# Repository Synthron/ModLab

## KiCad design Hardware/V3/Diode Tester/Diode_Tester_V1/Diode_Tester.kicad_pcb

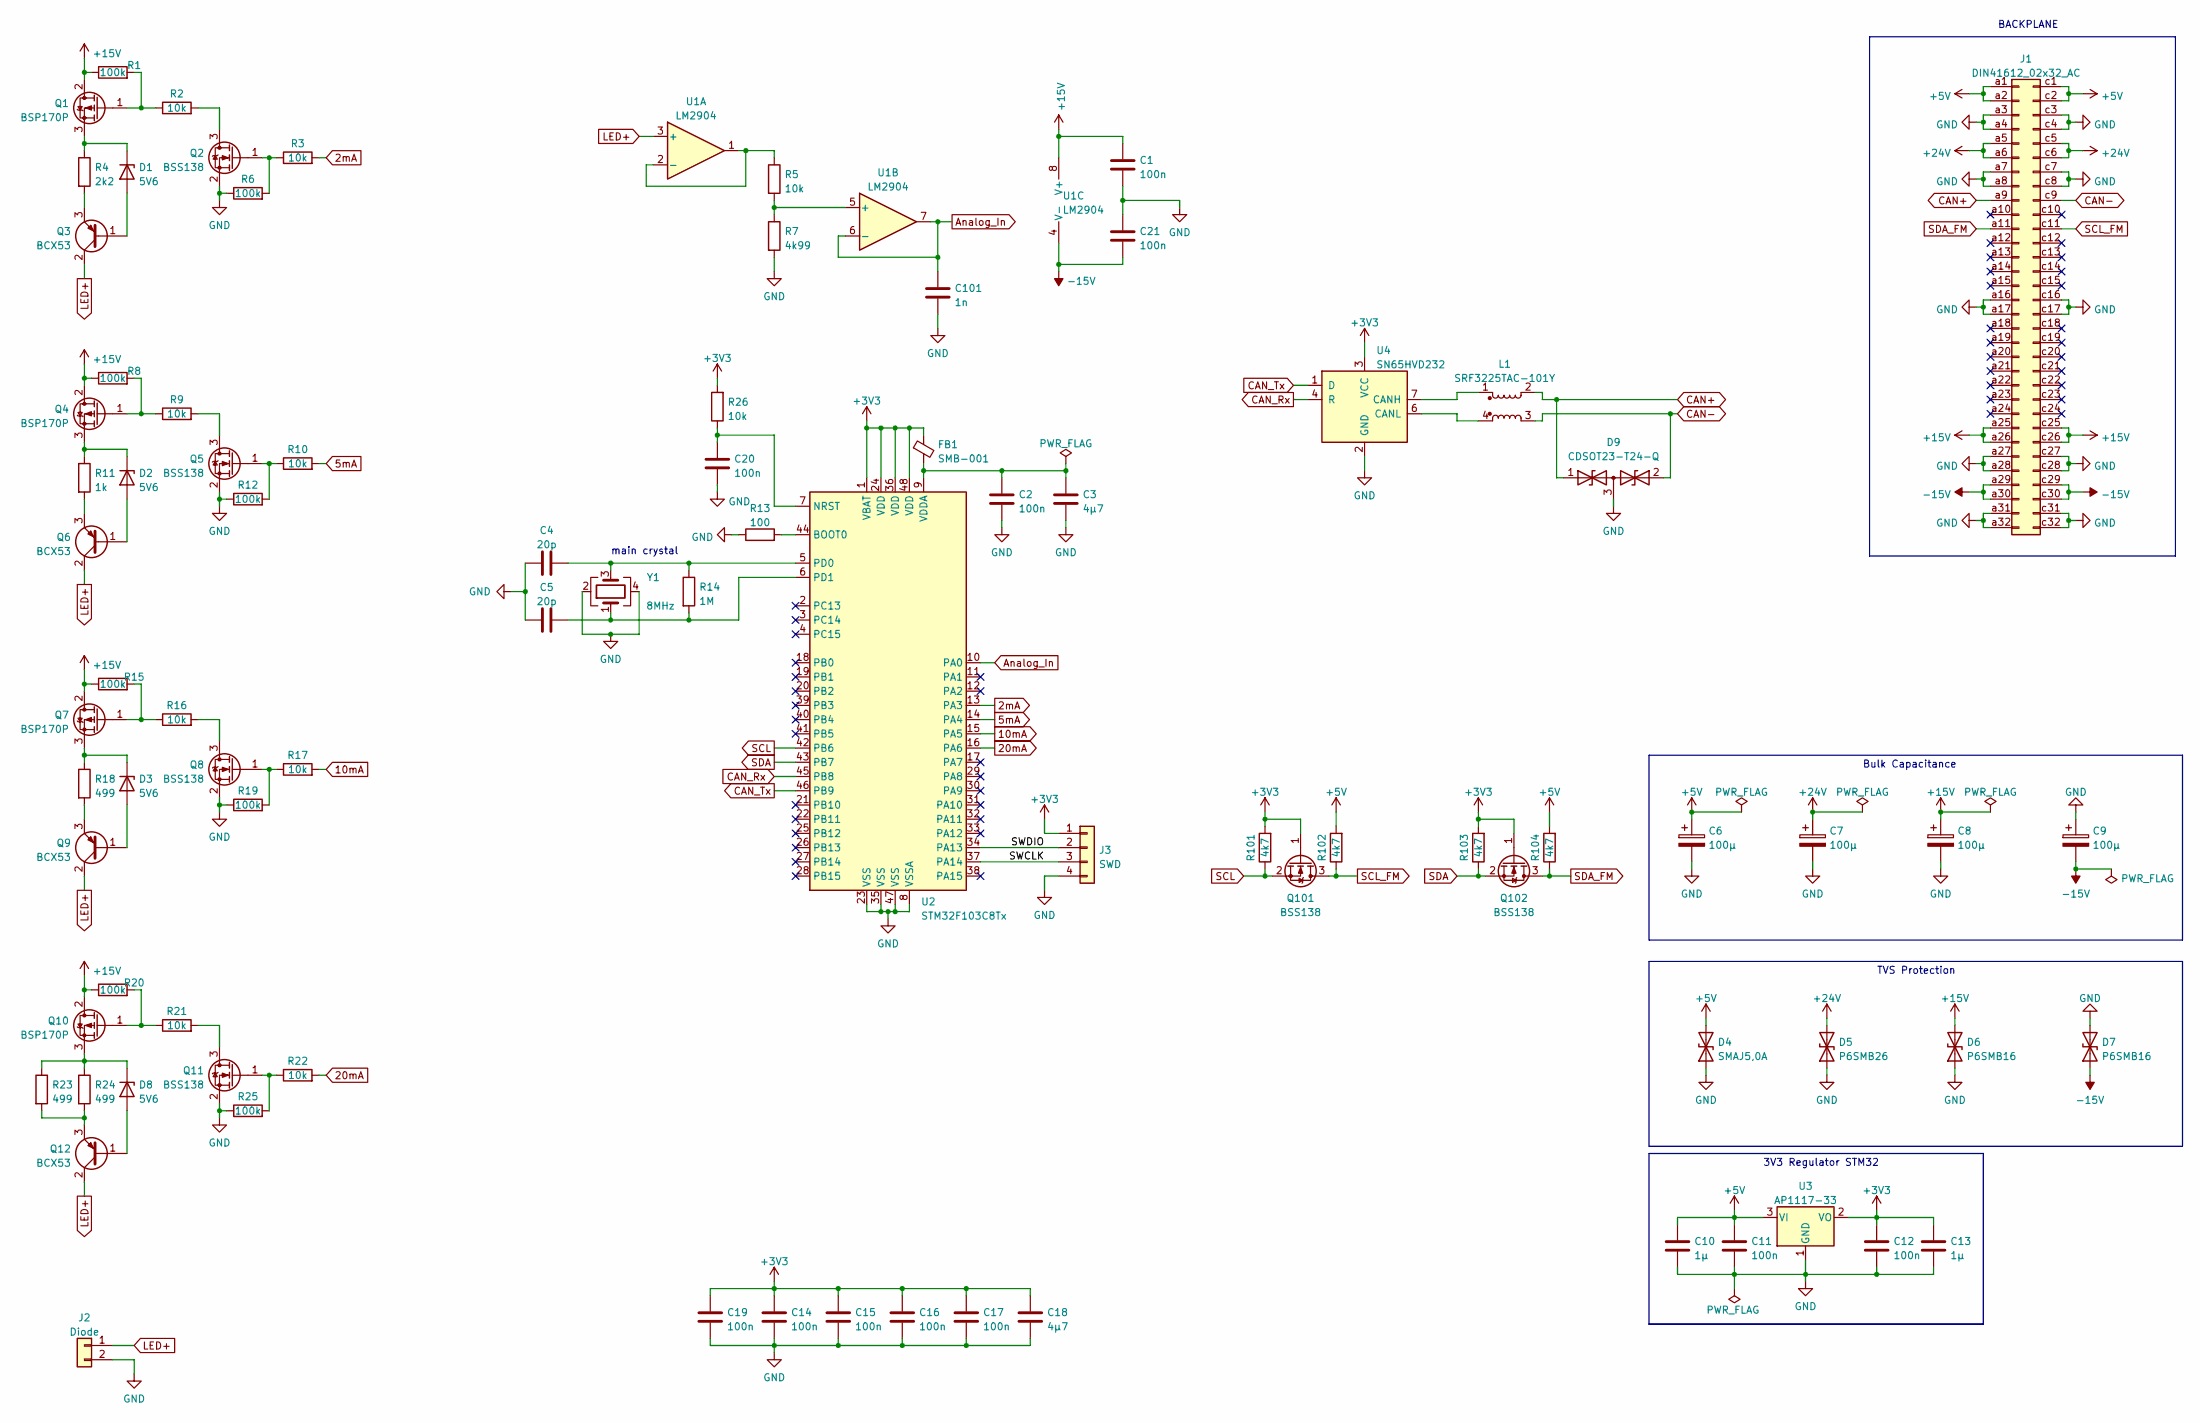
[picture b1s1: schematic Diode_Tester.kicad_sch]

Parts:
C1, C2, C11, C12, C14, C15, C16, C17, C19, C20, C21: 100n; C_0805_2012Metric
C3, C18: 4µ7; C_0805_2012Metric
C4, C5: 20p; C_0805_2012Metric
C6, C7, C8, C9: 100µ; CP_Radial_D8.0mm_P5.00mm
C10, C13: 1µ; C_0805_2012Metric
C101: 1n; C_0805_2012Metric
D1, D2, D3, D8: 5V6; D_MiniMELF
D4: SMAJ5,0A; D_SMA
D5: P6SMB26; D_SMA
D6, D7: P6SMB16; D_SMA
D9: CDSOT23-T24-Q; SOT-23
FB1: SMB-001
J1: DIN41612_02x32_AC; VG64_Euro
J2: Diode; PinHeader_1x02_P2.54mm_Vertical
J3: SWD; JST_XH_B4B-XH-A_1x04_P2.50mm_Vertical
L1: SRF3225TAC-101Y; SRF3225TAC
Q1, Q4, Q7, Q10: BSP170P; SOT-223-3_TabPin2
Q2, Q5, Q8, Q11, Q101, Q102: BSS138; SOT-23
Q3, Q6, Q9, Q12: BCX53; SOT-89-3
R1, R6, R8, R12, R15, R19, R20, R25: 100k; R_0805_2012Metric
R2, R3, R5, R9, R10, R16, R17, R21, R22, R26: 10k; R_0805_2012Metric
R4: 2k2; R_0805_2012Metric
R7: 4k99; R_0805_2012Metric
R11: 1k; R_0805_2012Metric
R13: 100; R_0805_2012Metric
R14: 1M; R_0805_2012Metric
R18, R23, R24: 499; R_0805_2012Metric
R101, R102, R103, R104: 4k7; R_0805_2012Metric
U1: LM2904; SOIC-8_3.9x4.9mm_P1.27mm
U2: STM32F103C8Tx; LQFP-48_7x7mm_P0.5mm
U3: AP1117-33; SOT-223-3_TabPin2
U4: SN65HVD232; SOIC-8_3.9x4.9mm_P1.27mm
Y1: 8MHz; Crystal_SMD_5032-4Pin_5.0x3.2mm

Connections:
2mA: R3.2, U2.13 (PA3)
5mA: R10.2, U2.14 (PA4)
10mA: R17.2, U2.15 (PA5)
20mA: R22.2, U2.16 (PA6)
+3V3: C12.1, C13.1, C14.1, C15.1, C16.1, C17.1, C18.1, C19.1, FB1.1, J3.1, Q101.1 (G), Q102.1 (G), R26.2, R101.2, R103.2, U2.1 (VBAT), U2.24 (VDD), U2.36 (VDD), U2.48 (VDD), U3.2 (VO), U4.3 (VCC)
+5V: C6.1, C10.1, C11.1, D4.2 (A2), J1.a1, J1.a2, J1.c1, J1.c2, R102.2, R104.2, U3.3 (VI)
+15V: C1.1, C8.1, D6.2 (A2), J1.a25, J1.a26, J1.c25, J1.c26, Q1.2 (D), Q4.2 (D), Q7.2 (D), Q10.2 (D), R1.1, R8.1, R15.1, R20.1, U1.8 (V+)
+24V: C7.1, D5.2 (A2), J1.a5, J1.a6, J1.c5, J1.c6
-15V: C9.2, C21.2, D7.1 (A1), J1.a29, J1.a30, J1.c29, J1.c30, U1.4 (V-)
/SWCLK: J3.3, U2.37 (PA14)
/SWDIO: J3.2, U2.34 (PA13)
Analog_In: C101.1, U1.6 (-), U1.7, U2.10 (PA0)
CAN+: D9.1 (A1), J1.a9, L1.2
CAN-: D9.2 (A2), J1.c9, L1.3
CAN_Rx: U2.45 (PB8), U4.4 (R)
CAN_Tx: U2.46 (PB9), U4.1 (D)
GND: C1.2, C2.2, C3.2, C4.1, C5.1, C6.2, C7.2, C8.2, C9.1, C10.2, C11.2, C12.2, C13.2, C14.2, C15.2, C16.2, C17.2, C18.2, C19.2, C20.2, C21.1, C101.2, D4.1 (A1), D5.1 (A1), D6.1 (A1), D7.2 (A2), D9.3 (common), J1.a3, J1.a4, J1.a7, J1.a8, J1.a16, J1.a17, J1.a27, J1.a28, J1.a31, J1.a32, J1.c3, J1.c4, J1.c7, J1.c8, J1.c16, J1.c17, J1.c27, J1.c28, J1.c31, J1.c32, J2.2, J3.4, Q2.2 (S), Q5.2 (S), Q8.2 (S), Q11.2 (S), R6.1, R7.2, R12.1, R13.1, R19.1, R25.1, U2.8 (VSSA), U2.23 (VSS), U2.35 (VSS), U2.47 (VSS), U3.1 (GND), U4.2 (GND), Y1.2, Y1.4
LED+: J2.1, Q3.2 (C), Q6.2 (C), Q9.2 (C), Q12.2 (C), U1.3 (+)
unnamed: C2.1, C3.1, FB1.2, U2.9 (VDDA)
unnamed: C4.2, R14.1, U2.5 (PD0), Y1.3
unnamed: C5.2, R14.2, U2.6 (PD1), Y1.1
unnamed: C20.1, R26.1, U2.7 (NRST)
unnamed: D1.1 (K), Q1.3 (S), R4.1
unnamed: D1.2 (A), Q3.1 (B)
unnamed: D2.1 (K), Q4.3 (S), R11.1
unnamed: D2.2 (A), Q6.1 (B)
unnamed: D3.1 (K), Q7.3 (S), R18.1
unnamed: D3.2 (A), Q9.1 (B)
unnamed: D8.1 (K), Q10.3 (S), R23.1, R24.1
unnamed: D8.2 (A), Q12.1 (B)
unnamed: L1.1, U4.7 (CANH)
unnamed: L1.4, U4.6 (CANL)
unnamed: Q1.1 (G), R1.2, R2.1
unnamed: Q2.1 (G), R3.1, R6.2
unnamed: Q2.3 (D), R2.2
unnamed: Q3.3 (E), R4.2
unnamed: Q4.1 (G), R8.2, R9.1
unnamed: Q5.1 (G), R10.1, R12.2
unnamed: Q5.3 (D), R9.2
unnamed: Q6.3 (E), R11.2
unnamed: Q7.1 (G), R15.2, R16.1
unnamed: Q8.1 (G), R17.1, R19.2
unnamed: Q8.3 (D), R16.2
unnamed: Q9.3 (E), R18.2
unnamed: Q10.1 (G), R20.2, R21.1
unnamed: Q11.1 (G), R22.1, R25.2
unnamed: Q11.3 (D), R21.2
unnamed: Q12.3 (E), R23.2, R24.2
unnamed: R5.1, U1.1, U1.2 (-)
unnamed: R5.2, R7.1, U1.5 (+)
unnamed: R13.2, U2.44 (BOOT0)
SCL: Q101.2 (S), R101.1, U2.42 (PB6)
SCL_FM: J1.c11, Q101.3 (D), R102.1
SDA: Q102.2 (S), R103.1, U2.43 (PB7)
SDA_FM: J1.a11, Q102.3 (D), R104.1

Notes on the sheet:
TVS Protection
3V3 Regulator STM32
main crystal
BACKPLANE
Bulk Capacitance

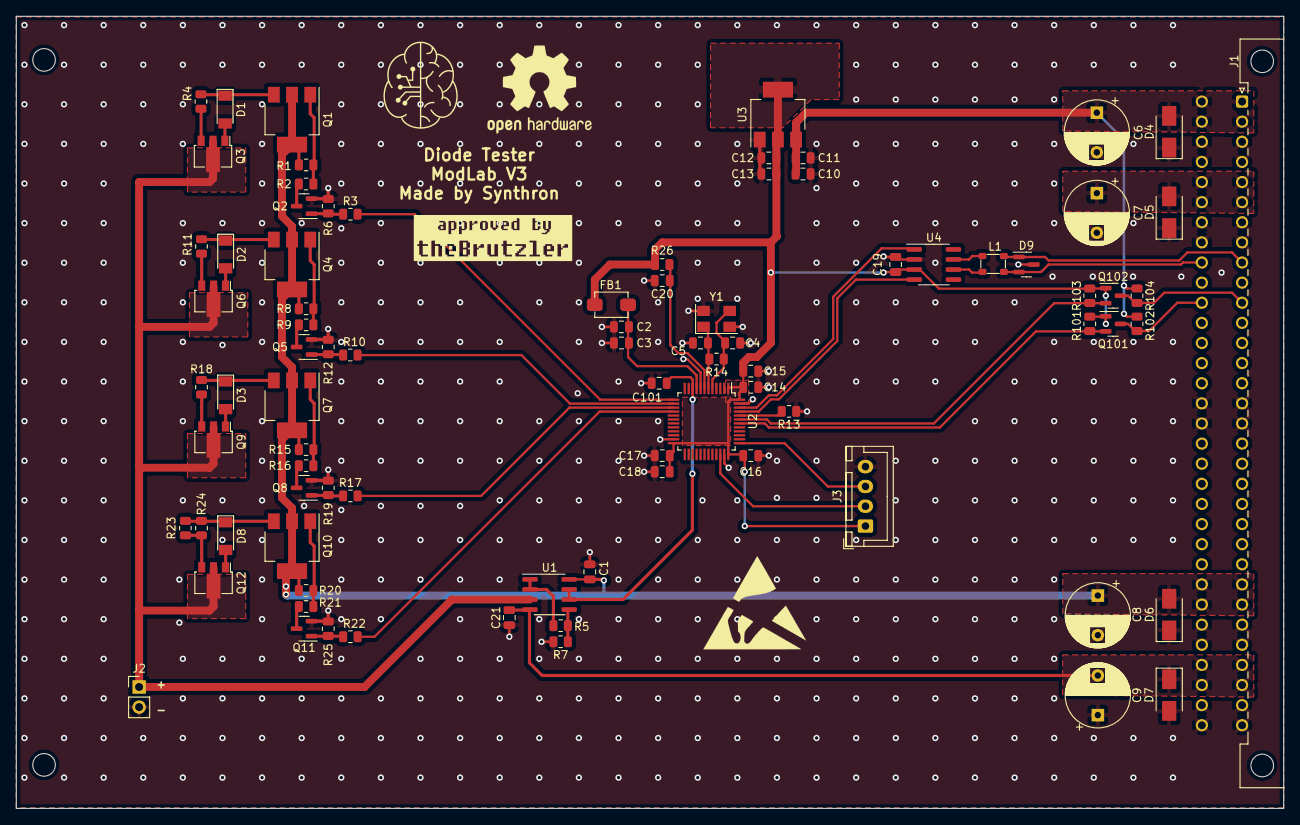
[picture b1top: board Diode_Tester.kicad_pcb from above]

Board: 2 copper layers, 160.0 x 100.0 mm, 85 parts (0 on the bottom side), 55 nets.

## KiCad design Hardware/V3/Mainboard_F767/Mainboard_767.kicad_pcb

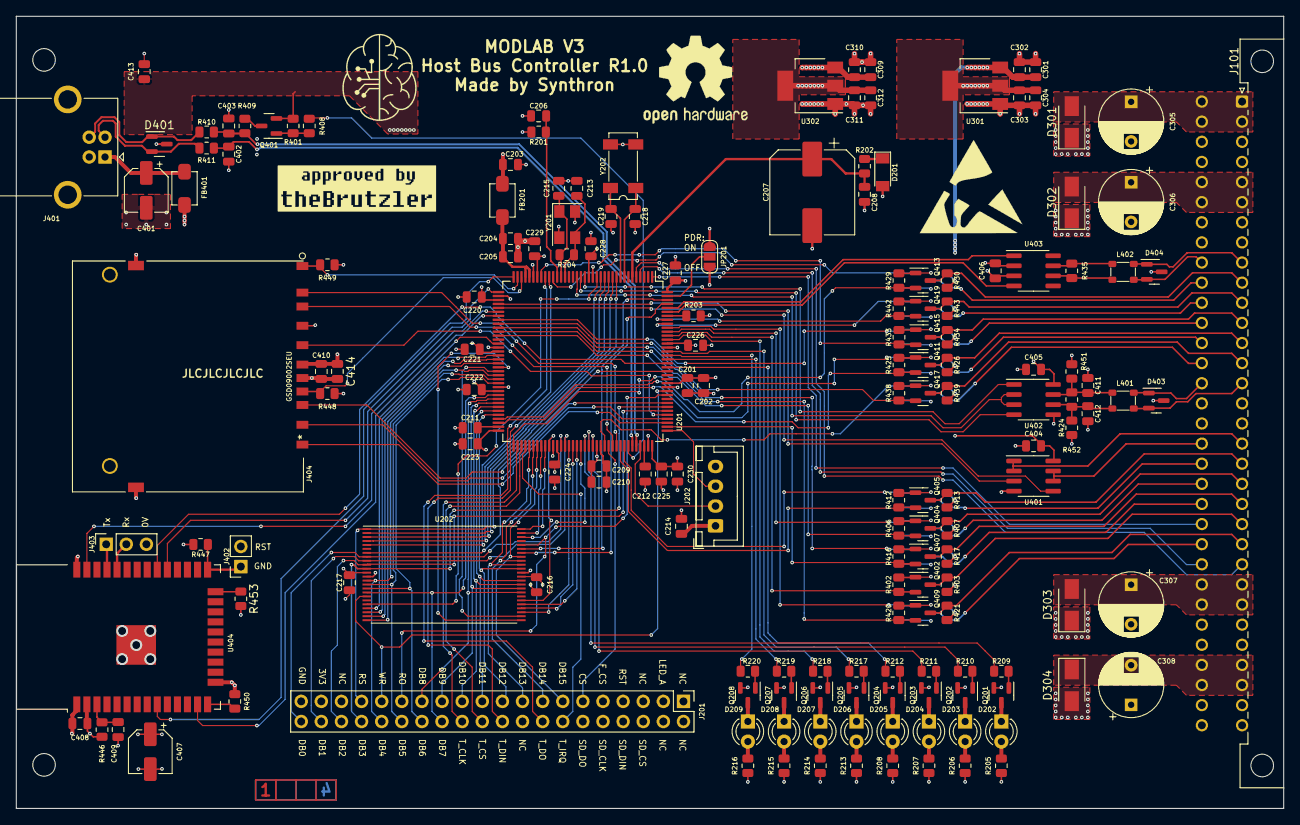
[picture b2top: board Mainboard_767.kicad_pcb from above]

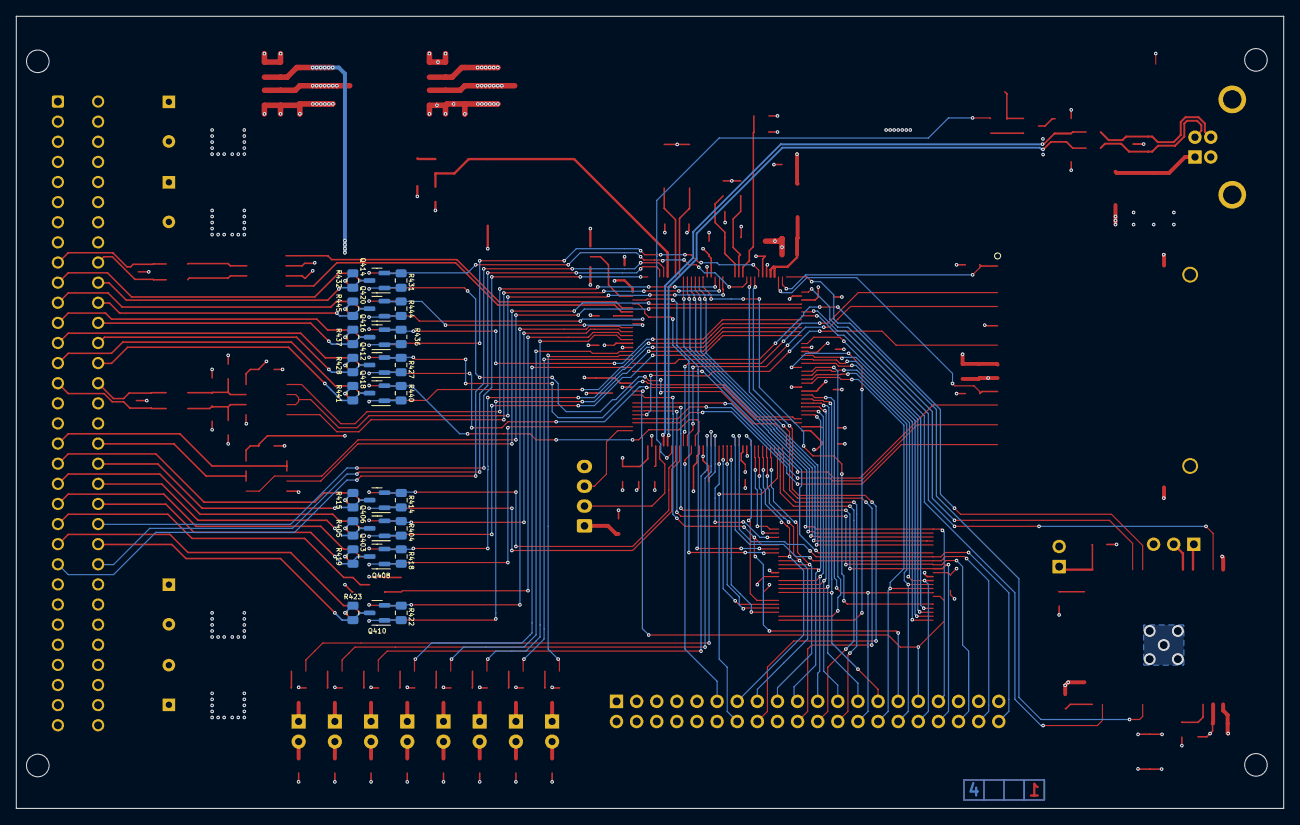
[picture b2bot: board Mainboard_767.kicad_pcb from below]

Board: 4 copper layers, 160.0 x 100.0 mm, 195 parts (27 on the bottom side), 184 nets.

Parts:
C201, C205, C206, C208, C209, C214, C216, C217, C220, C221, C222, C223, C224, C225, C226, C227, C228, C229, C302, C303, C310, C311, C404, C405, C406, C408, C410, C413: 100n; C_0805_2012Metric
C202, C203, C204, C210, C301, C304, C309, C312, C409, C414: 1µ; C_0805_2012Metric
C207: 0.22F/5V; CP_Elec_10x10.5
C211, C212: 2u2; C_0805_2012Metric
C213, C215: 20p; C_0805_2012Metric
C218, C219: 10p; C_0805_2012Metric
C230: 4µ7; C_0805_2012Metric
C305, C306, C307, C308: 100µ; CP_Radial_D8.0mm_P5.00mm
C401, C407: 10µ; CP_Elec_5x5.8
C402, C403: 47p; C_0805_2012Metric
C411, C412: 1n; C_0805_2012Metric
D201: LL4148; D_MiniMELF
D202, D203, D204, D205, D206, D207, D208, D209: LED; LED_D3.0mm
D301: SMAJ5,0A; D_SMA
D302: P6SMB26; D_SMA
D303, D304: P6SMB16; D_SMA
D401, D403, D404: CDSOT23-T24-Q; SOT-23
FB201, FB401: SMB-001
J101: DIN41612_02x32_AC; VG64_Euro
J201: LCD; PinHeader_2x20_P2.54mm_Vertical
J202: SWD; JST_XH_B4B-XH-A_1x04_P2.50mm_Vertical
J401: USB_B; USB_B_OST_USB-B1HSxx_Horizontal
J402: Boot_Option; PinSocket_1x02_P2.54mm_Vertical
J403: ESP UART; PinSocket_1x03_P2.54mm_Vertical
J404: GSD09002SEU
JP201: PDR_ON Jumper; SolderJumper-3_P1.3mm_Open_RoundedPad1.0x1.5mm_NumberLabels
L401, L402: SRF3225TAC-101Y; SRF3225TAC
Q201, Q202, Q203, Q204, Q205, Q206, Q207, Q208, Q402, Q403, Q404, Q405, Q406, Q407, Q408, Q409, Q410, Q411, Q412, Q413, Q414, Q415, Q416, Q417, Q418, Q419, Q420: BSS138; SOT-23
Q401: BC856; SOT-23
R201, R209, R210, R211, R212, R217, R218, R219, R220, R412, R413, R414, R415, R416, R417, R418, R419, R420, R421, R422, R423, R429, R430, R431, R432, R433, R434, R436, R437, R438, R439, R440, R441, R446: 10k; R_0805_2012Metric
R202, R203: 100; R_0805_2012Metric
R204: 1M; R_0805_2012Metric
R205, R206, R207, R208, R213, R214, R215, R216, R402, R403, R404, R405, R406, R407, R447, R448, R449, R450, R453: 1k; R_0805_2012Metric
R401, R408: 100k; R_0805_2012Metric
R409: 1k5; R_0805_2012Metric
R410, R411: 22; R_0805_2012Metric
R424, R435: 120; R_0805_2012Metric
R425, R426, R427, R428, R451, R452: 4k7; R_0805_2012Metric
R442, R443, R444, R445: 3k3; R_0805_2012Metric
U201: STM32F767ZITx; LQFP-144_20x20mm_P0.5mm
U202: IS61WV5126EEBLL-10T2LI; TSOP-I-48_18.4x12mm_P0.5mm
U301, U302: AP1117-33; SOT-223-3_TabPin2
U401: LM2904; SOIC-8_3.9x4.9mm_P1.27mm
U402: MAX485E; SOIC-8_3.9x4.9mm_P1.27mm
U403: SN65HVD232; SOIC-8_3.9x4.9mm_P1.27mm
U404: ESP32-WROOM-32
Y201: 8MHz; Crystal_SMD_5032-4Pin_5.0x3.2mm
Y202: 32.768kHz; Crystal_SMD_SeikoEpson_MC306-4Pin_8.0x3.2mm

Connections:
+3.3V: C311.1, C312.1, C407.1, C408.1, R446.1, R447.1, U302.2 (VO), U404.2 (VDD)
+3V3: C201.1, C202.1, C203.1, C209.1, C210.1, C214.1, C216.1, C217.1, C220.1, C221.1, C222.1, C223.1, C224.1, C225.1, C226.1, C227.1, C228.1, C229.1, C230.1, C303.1, C304.1, C405.1, C406.1, C410.1, C413.1, C414.1, D201.2 (A), FB201.1, J201.3, J201.6, J201.7, J201.9, J201.37, J202.1, J404.4 (VDD), JP201.3 (B), Q401.2 (E), Q402.1 (G), Q403.1 (G), Q404.1 (G), Q405.1 (G), Q406.1 (G), Q407.1 (G), Q408.1 (G), Q409.1 (G), Q410.1 (G), Q411.1 (G), Q412.1 (G), Q413.1 (G), Q414.1 (G), Q415.1 (G), Q416.1 (G), Q417.1 (G), Q418.1 (G), Q419.1 (G), Q420.1 (G), R201.1, R205.1, R206.1, R207.1, R208.1, R213.1, R214.1, R215.1, R216.1, R401.2, R402.1, R404.1, R406.1, R412.1, R414.1, R416.1, R418.1, R420.1, R422.1, R425.1, R427.1, R429.1, R431.1, R433.1, R436.1, R438.1, R440.1, R442.1, R444.1, R448.1, R449.1, R451.1, U201.17 (VDD), U201.30 (VDD), U201.39 (VDD), U201.52 (VDD), U201.62 (VDD), U201.72 (VDD), U201.84 (VDD), U201.95 (VDDUSB), U201.108 (VDD), U201.121 (VDDSDMMC), U201.131 (VDD), U201.144 (VDD), U202.12 (VDD), U202.36 (VDD), U301.2 (VO), U402.8 (VCC), U403.3 (VCC)
+5V: C301.1, C302.1, C305.1, C309.1, C310.1, C404.1, D301.2 (A2), FB401.2, J101.a1, J101.a2, J101.c1, J101.c2, R403.1, R405.1, R407.1, R413.1, R415.1, R417.1, R419.1, R421.1, R423.1, R426.1, R428.1, R430.1, R432.1, R434.1, R437.1, R439.1, R441.1, R443.1, R445.1, U301.3 (VI), U302.3 (VI), U401.8 (V+)
+15V: C307.1, D303.2 (A2), J101.a25, J101.a26, J101.c25, J101.c26
+24V: C306.1, D302.2 (A2), J101.a5, J101.a6, J101.c5, J101.c6
-15V: C308.2, D304.1 (A1), J101.a29, J101.a30, J101.c29, J101.c30
/CPU/CAN1_RX: U201.139 (PB8), U403.4 (R)
/CPU/CAN1_TX: U201.140 (PB9), U403.1 (D)
/CPU/CS_0: Q405.2 (S), R412.2, U201.100 (PA8)
/CPU/CS_1: Q406.2 (S), R414.2, U201.101 (PA9)
/CPU/CS_2: Q407.2 (S), R416.2, U201.110 (PA15)
/CPU/CS_3: Q408.2 (S), R418.2, U201.46 (PB0)
/CPU/CS_4: Q409.2 (S), R420.2, U201.47 (PB1)
/CPU/CS_5: Q410.2 (S), R422.2, U201.135 (PB5)
/CPU/DAC_OUT1: U201.40 (PA4), U401.3 (+)
/CPU/DAC_OUT2: U201.41 (PA5), U401.5 (+)
/CPU/ESP32_CS: U201.37 (PA3), U404.29 (IO5)
/CPU/ESP32_RDY: U201.36 (PA2), U404.9 (IO33)
/CPU/I2C1FM_SCL: Q420.2 (S), R444.2, U201.136 (PB6)
/CPU/I2C2_SCL: Q412.2 (S), R427.2, U201.69 (PB10)
/CPU/I2C2_SDA: Q411.2 (S), R425.2, U201.70 (PB11)
/CPU/I2CFM_SDA: Q419.2 (S), R442.2, U201.137 (PB7)
/CPU/IO_0: Q413.2 (S), R429.2, U201.73 (PB12)
/CPU/IO_1: Q414.2 (S), R431.2, U201.26 (PC0)
/CPU/IO_2: Q415.2 (S), R433.2, U201.29 (PC3)
/CPU/IO_3: Q416.2 (S), R436.2, U201.44 (PC4)
/CPU/IO_4: Q417.2 (S), R438.2, U201.45 (PC5)
/CPU/IO_5: Q418.2 (S), R440.2, U201.96 (PC6)
/CPU/PDR_ON: JP201.2 (C), U201.143 (PDR_ON)
/CPU/RESET: C206.1, R201.2, U201.25 (NRST)
/CPU/SD1_CK: J404.5 (CLK), U201.113 (PC12)
/CPU/SD1_CMD: J404.2 (CMD), U201.116 (PD2)
/CPU/SD1_D0: J404.7 (DAT0), U201.98 (PC8)
/CPU/SD1_D1: J404.8 (DAT1), U201.99 (PC9)
/CPU/SD1_D2: J404.9 (DAT2), U201.111 (PC10)
/CPU/SD1_D3: J404.1 (CD/DAT3), U201.112 (PC11)
/CPU/SPI1_MISO: U201.42 (PA6), U404.37 (IO23)
/CPU/SPI1_MOSI: U201.43 (PA7), U404.13 (IO14)
/CPU/SPI1_SCK: U201.126 (PG11), U404.30 (IO18)
/CPU/SPI3_MISO: Q403.2 (S), R404.2, U201.134 (PB4)
/CPU/SPI3_MOSI: Q404.2 (S), R406.2, U201.48 (PB2)
/CPU/SPI3_SCK: Q402.2 (S), R402.2, U201.133 (PB3)
/CPU/SWCLK: J202.3, U201.109 (PA14)
/CPU/SWDIO: J202.2, U201.105 (PA13)
/CPU/UART7_DE_485: U201.20 (PF8), U402.2 (~RE), U402.3 (DE)
/CPU/UART7_RX_485: U201.18 (PF6), U402.1 (RO)
/CPU/UART7_TX_485: U201.19 (PF7), U402.4 (DI)
/CPU/USB+: C403.1, R409.1, R410.2, U201.104 (PA12)
/CPU/USB-: C402.1, R411.2, U201.103 (PA11)
/CPU/USB_Disconnect: R408.1, U201.102 (PA10)
/CPU/VBAT: C207.1, C208.1, R202.2, U201.6 (VBAT)
/CPU/VDDA: C204.1, C205.1, FB201.2, U201.32 (VREF+), U201.33 (VDDA)
/CPU//SD_Card_Detect: J404.10 (CARD_DETECT), R448.2, U201.34 (PA0)
/CPU//SD_Write_Protect: J404.15 (Write_Protect), R449.2, U201.35 (PA1)
/Peripherals/ESP_RX: J403.2, U404.34 (RXD0/IO3)
/Peripherals/ESP_TX: J403.1, U404.35 (TXD0/IO1)
CAN+: D404.1 (A1), J101.a9, L402.2
CAN-: D404.2 (A2), J101.c9, L402.3
CS0: J101.a19, Q405.3 (D), R413.2
CS1: J101.c19, Q406.3 (D), R415.2
CS2: J101.a21, Q407.3 (D), R417.2
CS3: J101.c21, Q408.3 (D), R419.2
CS4: J101.a23, Q409.3 (D), R421.2
CS5: J101.c23, Q410.3 (D), R423.2
DAC1_OUT: J101.a18, U401.1, U401.2 (-)
DAC2_OUT: J101.c18, U401.6 (-), U401.7
FMC_A0: J201.33, U201.10 (PF0), U202.1 (A0)
FMC_A1: U201.11 (PF1), U202.2 (A1)
FMC_A2: U201.12 (PF2), U202.3 (A2)
FMC_A3: U201.13 (PF3), U202.4 (A3)
FMC_A4: U201.14 (PF4), U202.5 (A4)
FMC_A5: U201.15 (PF5), U202.20 (A5)
FMC_A6: U201.50 (PF12), U202.21 (A6)
FMC_A7: U201.53 (PF13), U202.22 (A7)
FMC_A8: U201.54 (PF14), U202.23 (A8)
FMC_A9: U201.55 (PF15), U202.24 (A9)
FMC_A10: U201.56 (PG0), U202.25 (A10)
FMC_A11: U201.57 (PG1), U202.26 (A11)
FMC_A12: U201.87 (PG2), U202.27 (A12)
FMC_A13: U201.88 (PG3), U202.28 (A13)
FMC_A14: U201.89 (PG4), U202.29 (A14)
FMC_A15: U201.90 (PG5), U202.46 (A15)
FMC_A16: U201.80 (PD11), U202.47 (A16)
FMC_A17: U201.81 (PD12), U202.48 (A17)
FMC_A18: U201.82 (PD13), U202.30 (A18)
FMC_D0: J201.40, U201.85 (PD14), U202.8 (D0)
FMC_D1: J201.38, U201.86 (PD15), U202.9 (D1)
FMC_D2: J201.36, U201.114 (PD0), U202.10 (D2)
FMC_D3: J201.34, U201.115 (PD1), U202.11 (D3)
FMC_D4: J201.32, U201.58 (PE7), U202.14 (D4)
FMC_D5: J201.30, U201.59 (PE8), U202.15 (D5)
FMC_D6: J201.28, U201.60 (PE9), U202.16 (D6)
FMC_D7: J201.26, U201.63 (PE10), U202.17 (D7)
FMC_D8: J201.27, U201.64 (PE11), U202.32 (D8)
FMC_D9: J201.25, U201.65 (PE12), U202.33 (D9)
FMC_D10: J201.23, U201.66 (PE13), U202.34 (D10)
FMC_D11: J201.21, U201.67 (PE14), U202.35 (D11)
FMC_D12: J201.19, U201.68 (PE15), U202.38 (D12)
FMC_D13: J201.17, U201.77 (PD8), U202.39 (D13)
FMC_D14: J201.15, U201.78 (PD9), U202.40 (D14)
FMC_D15: J201.13, U201.79 (PD10), U202.41 (D15)
FMC_NBL0: U201.141 (PE0), U202.42 (/LB)
FMC_NBL1: U201.142 (PE1), U202.43 (/UB)
FMC_NE1: J201.11, U201.97 (PC7)
FMC_NE2: U201.124 (PG9), U202.7 (/CS)
FMC_NOE: J201.29, U201.118 (PD4), U202.44 (/OE)
FMC_NWE: J201.31, U201.119 (PD5), U202.18 (/WE)
GND: C201.2, C202.2, C203.2, C204.2, C205.2, C206.2, C207.2, C208.2, C209.2, C210.2, C211.2, C212.2, C213.1, C214.2, C215.1, C216.2, C217.2, C218.1, C219.1, C220.2, C221.2, C222.2, C223.2, C224.2, C225.2, C226.2, C227.2, C228.2, C229.2, C230.2, C301.2, C302.2, C303.2, C304.2, C305.2, C306.2, C307.2, C308.1, C309.2, C310.2, C311.2, C312.2, C401.2, C402.2, C403.2, C404.2, C405.2, C406.2, C407.2, C408.2, C409.2, C410.2, C411.1, C412.2, C413.2, C414.2, D301.1 (A1), D302.1 (A1), D303.1 (A1), D304.2 (A2), D401.3 (common), D403.3 (common), D404.3 (common), J101.a3, J101.a4, J101.a7, J101.a8, J101.a16, J101.a17, J101.a27, J101.a28, J101.a31, J101.a32, J101.c3, J101.c4, J101.c7, J101.c8, J101.c16, J101.c17, J101.c27, J101.c28, J101.c31, J101.c32, J201.39, J202.4, J401.4 (GND), J401.5 (Shield), J402.2, J403.3, J404.3 (VSS), J404.6 (VSS), J404.11 (WRITE_PROTECT), J404.12 (SHELL1), JP201.1 (A), Q201.2 (S), Q202.2 (S), Q203.2 (S), Q204.2 (S), Q205.2 (S), Q206.2 (S), Q207.2 (S), Q208.2 (S), R203.1, R450.2, R452.2, R453.2, U201.16 (VSS), U201.31 (VSSA), U201.38 (VSS), U201.51 (VSS), U201.61 (VSS), U201.83 (VSS), U201.94 (VSS), U201.107 (VSS), U201.120 (VSS), U201.130 (VSS), U202.13 (VSS), U202.37 (VSS), U301.1 (GND), U302.1 (GND), U401.4 (V-), U402.5 (GND), U403.2 (GND), U404.1 (GND), U404.15 (GND), U404.38 (GND), U404.39 (GND), Y201.2, Y201.4, Y202.2, Y202.3
IO0: J101.a10, Q413.3 (D), R430.2
IO1: J101.c10, Q414.3 (D), R432.2
IO2: J101.a12, Q415.3 (D), R434.2
IO3: J101.c12, Q416.3 (D), R437.2
IO4: J101.a14, Q417.3 (D), R439.2
IO5: J101.c14, Q418.3 (D), R441.2
LED_485: R210.2, U201.92 (PG7)
LED_CAN: R209.2, U201.91 (PG6)
LED_ESP: R219.2, U201.127 (PG12)
LED_I2C1: R211.2, U201.93 (PG8)
LED_I2C2: R212.2, U201.125 (PG10)
LED_SD: R220.2, U201.128 (PG13)
LED_SPI3: R217.2, U201.129 (PG14)
LED_SPI4: R218.2, U201.132 (PG15)
MISO3: J101.c20, Q403.3 (D), R405.2
MISO4: J101.c24, U201.4 (PE5)
MOSI3: J101.a20, Q404.3 (D), R407.2
MOSI4: J101.a24, U201.5 (PE6)
unnamed: C211.1, U201.71 (VCAP_1)
unnamed: C212.1, U201.106 (VCAP_2)
unnamed: C213.2, R204.1, U201.23 (PH0), Y201.3
unnamed: C215.2, R204.2, U201.24 (PH1), Y201.1
unnamed: C218.2, U201.8 (PC14), Y202.1
unnamed: C219.2, U201.9 (PC15), Y202.4
unnamed: C401.1, FB401.1, J401.1 (VBUS)
unnamed: C409.1, R446.2, U404.3 (EN)
unnamed: C411.2, L401.1, R424.1, R451.2, U402.7 (B)
unnamed: C412.1, L401.4, R424.2, R452.1, U402.6 (A)
unnamed: D201.1 (K), R202.1
unnamed: D202.1 (K), Q201.3 (D)
unnamed: D202.2 (A), R205.2
unnamed: D203.1 (K), Q202.3 (D)
unnamed: D203.2 (A), R206.2
unnamed: D204.1 (K), Q203.3 (D)
unnamed: D204.2 (A), R207.2
unnamed: D205.1 (K), Q204.3 (D)
unnamed: D205.2 (A), R208.2
unnamed: D206.1 (K), Q205.3 (D)
unnamed: D206.2 (A), R213.2
unnamed: D207.1 (K), Q206.3 (D)
unnamed: D207.2 (A), R214.2
unnamed: D208.1 (K), Q207.3 (D)
unnamed: D208.2 (A), R215.2
unnamed: D209.1 (K), Q208.3 (D)
unnamed: D209.2 (A), R216.2
unnamed: D401.2 (A2), J401.2 (D-), R411.1
unnamed: D401.1 (A1), J401.3 (D+), R410.1
unnamed: J402.1, R447.2, U404.25 (IO0)
unnamed: L402.1, R435.1, U403.7 (CANH)
unnamed: L402.4, R435.2, U403.6 (CANL)
unnamed: Q201.1 (G), R209.1
unnamed: Q202.1 (G), R210.1
unnamed: Q203.1 (G), R211.1
unnamed: Q204.1 (G), R212.1
unnamed: Q205.1 (G), R217.1
unnamed: Q206.1 (G), R218.1
unnamed: Q207.1 (G), R219.1
unnamed: Q208.1 (G), R220.1
unnamed: Q401.1 (B), R401.1, R408.2
unnamed: Q401.3 (C), R409.2
unnamed: R203.2, U201.138 (BOOT0)
unnamed: R450.1, U404.14 (IO12)
unnamed: R453.1, U404.24 (IO2)
RS485+: D403.2 (A2), J101.a15, L401.3
RS485-: D403.1 (A1), J101.c15, L401.2
SCK3: J101.a22, Q402.3 (D), R403.2
SCK4: J101.c22, U201.1 (PE2)
SCL: J101.c13, Q412.3 (D), R428.2
SCL_FM: J101.c11, Q420.3 (D), R445.2
SDA: J101.a13, Q411.3 (D), R426.2
SDA_FM: J101.a11, Q419.3 (D), R443.2
SPI2_MISO: J201.16, U201.28 (PC2)
SPI2_MOSI: J201.20, U201.27 (PC1)
SPI2_SCK: J201.24, U201.74 (PB13)
Touch_CS: J201.22, U201.75 (PB14)
Touch_IRQ: J201.14, U201.76 (PB15)

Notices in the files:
parts and their libraries:
Copyright 2021 Accelerated Designs. All rights reserved.
